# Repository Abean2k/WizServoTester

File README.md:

# WizServoTester

A servo controller PCB that can control up to 4 servos using onboard rotary encoders. Powered by an ESP32-C6 with two power input modes, USB and FTC 12V Battery. 

## Design and Inspo:
I wanted to solve the issue that my team and many other FTC teams I know have. When testing Gobiulda Servos (such as during Robot In 3 Days) we need a fast way to move multiple servos without using code. 
Currently, the only solution available is from Gobiulda, and the full kit for 4 servos cost about $200. So, I made WizServotester!

When designing this I made sure to keep it useful to FTC teams by allowing teams to use their existing battery to power the device. Teams already have many 12v 10 cell batteries, so I have included the xt30 connector that all these batteries have and a buck converter to step the voltage down to 5v for use in the circuit. The entire thing can be reprogrammed using the USBc and inbuilt USB programmer on the ESP32-C6. 

### Power:
This thing can be powered in two ways - USB & Battery. When under battery power all 4 servos can be used at full load and in both continuous and normal modes. However, when in USB power, only 1 servo can be used at one time. This is due to the limited power capacity of a USB C cable. Power can be selected using a switch on the pcb.  

## PCB:
I made a 2 layered PCB on Kicad for the servo tester. The pcb is around 100mm by 60mm. I have included some instructions on how to use the power switch and battery connector as well as some PCB Art (my first time trying that out <3). 

### Schematic

### PCB Layout

## Case:
This is optional, if you are recreating this project, you can choose to use my case or just not use a case. Made with two parts, a base, and a top cover type thing. Uses m3 screws to fasten the PCB into the case and the bottom of the base to the top. Designed on Onshape. 

## Firmware:
The ESP32 will run C++ with Arduino. The code is still under development. The idea is that the code can detect the voltage of the USDB to see where it's receiving power from, then it can control the servos based on the position of the rotary encoder. Lots of the code is similar to my rocketry airbrake project so V1 code development was quick. The online app that is hosted on the ESP will be added based on how the PCB performs and feedback I receive from my team about the tester. 

## Bill of Materials (BOM)

| Part | Quantity | Retailer | Total Price |
|---|---|---|---|
| ESP32-C6-WROOM-1 | 1x5 | LCSC | $21.16 |
| SMD Caps (10u, 100n, 1u, 22u) | 9 x 5 | Already have | $0.00 |
| 470u 16v Capacitor | 1x5 | LCSC | $0.61 |
| ESD9B3.3 Diode | 2x5 | LCSC | $0.53 |
| SS34 Schottky Diode | 1x5 | LCSC | $0.71 |
| SS54 Schottky Diode | 1x5 | LCSC | $0.45 |
| USB-C Receptacle | 1x5 | LCSC | $0.62 |
| XT30 Battery Connector | 1x5 | AliExpress | $2.97 |
| (01x03) Male 90 Degree Header | 4x5 | AliExpress | $5.58 |
| Resistors (10k, 5.1k, 4.7k) | 30 | Already have | $0.00 |
| EC11 Rotary Encoder | 4x5 | AliExpress | $3.24 |
| Push Button Switch | 2x5 | LCSC | $0.53 |
| SPDT Power Select Switch ($1.84) | 1x5 | LCSC | $1.84 |
| USBLC6-2SC6 (USB Protection) | 1x5 | LCSC | $0.48 |
| AMS1117-3.3 (LDO) | 1x5 | LCSC | $0.49 |
| Mini560 Buck Converter | 1x5 | AliExpress | $4.40 |
| PCB (5x boards) | 1x5 | LCSC | $11.32 |

**Taxes & Shipping: AliExpress ($0.96) + LCSC ($10.80)** 

**Total Cost For 5 PCBS: $66.69**

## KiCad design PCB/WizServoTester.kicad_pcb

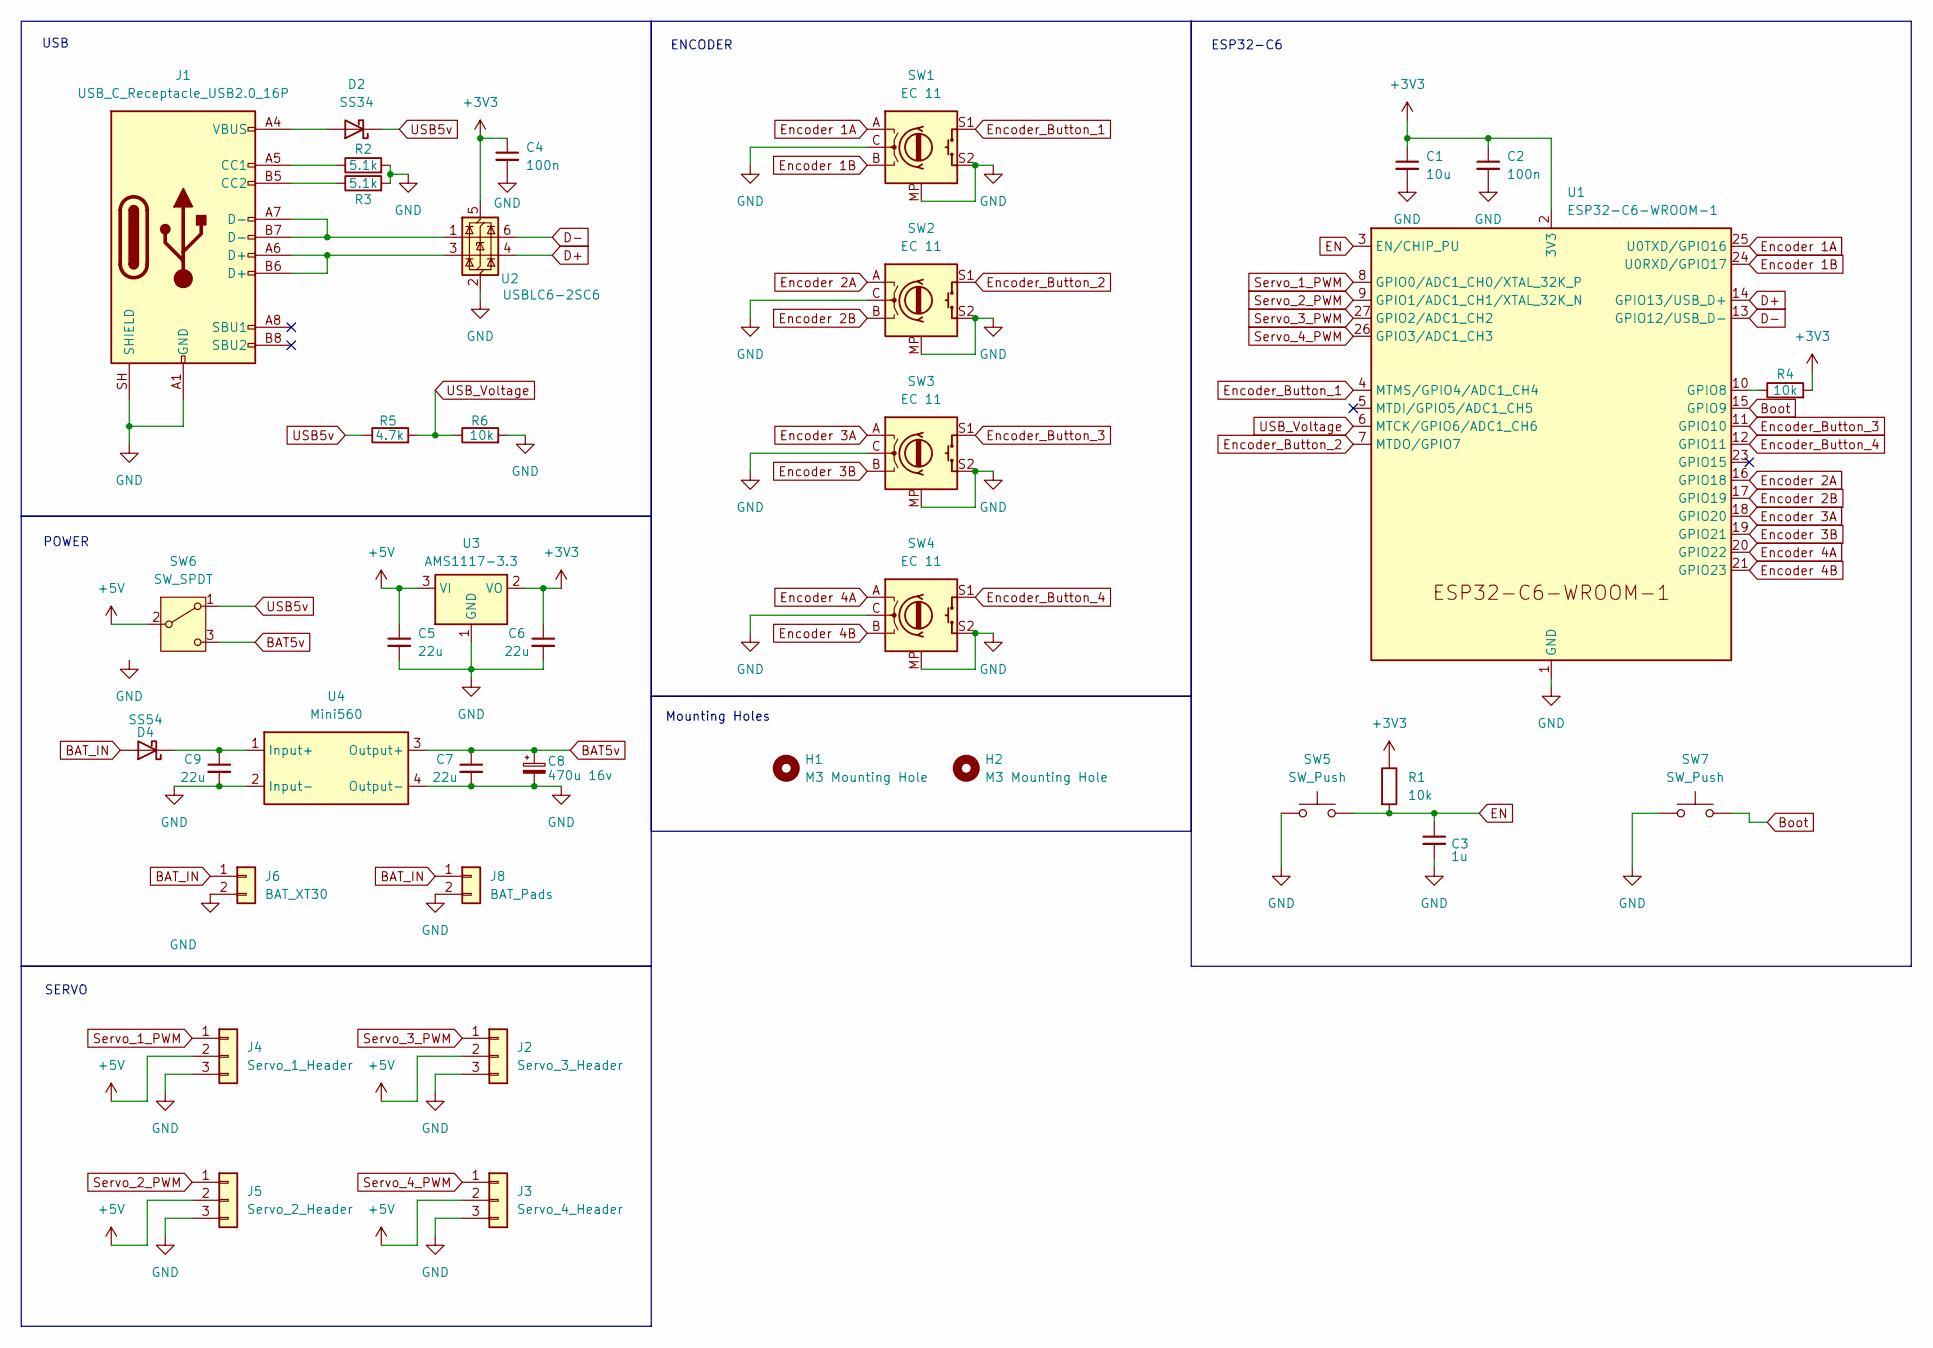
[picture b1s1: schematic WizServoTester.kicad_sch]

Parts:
C1: 10u; C_0805_2012Metric
C2, C4: 100n; C_0805_2012Metric
C3: 1u; C_0805_2012Metric
C5, C6, C7, C9: 22u; C_0805_2012Metric
C8: 470u 16v; CP_Elec_8x10.5
D2: SS34; D_SMA
D4: SS54; D_SMA
H1, H2: M3 Mounting Hole; MountingHole_3.2mm_M3
J1: USB_C_Receptacle_USB2.0_16P; USB_C_Receptacle_HCTL_HC-TYPE-C-16P-01A
J2: Servo_3_Header; PinHeader_1x03_P2.54mm_Horizontal
J3: Servo_4_Header; PinHeader_1x03_P2.54mm_Horizontal
J4: Servo_1_Header; PinHeader_1x03_P2.54mm_Horizontal
J5: Servo_2_Header; PinHeader_1x03_P2.54mm_Horizontal
J6: BAT_XT30; AMASS_XT30U-F_1x02_P5.0mm_Vertical
J8: BAT_Pads; TestPoint_2Pads_Pitch5.08mm_Drill1.3mm
R1, R4, R6: 10k; R_0805_2012Metric
R2, R3: 5.1k; R_0805_2012Metric
R5: 4.7k; R_0805_2012Metric
SW1, SW2, SW3, SW4: EC 11; RotaryEncoder_Alps_EC11E-Switch_Vertical_H20mm_MountingHoles
SW5, SW7: SW_Push; SW_SPST_TS-1088-xR020
SW6: SW_SPDT; SW-TH_XKB_SS-12M11XX
U1: ESP32-C6-WROOM-1
U2: USBLC6-2SC6; SOT-23-6
U3: AMS1117-3.3; SOT-223-3_TabPin2
U4: Mini560; mini650

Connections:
+3V3: C1.1, C2.1, C4.1, C6.1, R1.1, R4.2, U1.2 (3V3), U2.5 (VBUS), U3.2 (VO)
+5V: C5.1, J2.2, J3.2, J4.2, J5.2, SW6.2 (B), U3.3 (VI)
BAT5v: C7.1, C8.1, SW6.3 (C), U4.3 (Output+)
BAT_IN: D4.2 (A), J6.1, J8.1
Boot: SW7.2, U1.15 (GPIO9)
D+: U1.14 (GPIO13/USB_D+), U2.4 (I/O2)
D-: U1.13 (GPIO12/USB_D-), U2.6 (I/O1)
EN: C3.1, R1.2, SW5.2, U1.3 (EN/CHIP_PU)
Encoder 1A: SW1.A, U1.25 (U0TXD/GPIO16)
Encoder 1B: SW1.B, U1.24 (U0RXD/GPIO17)
Encoder 2A: SW2.A, U1.16 (GPIO18)
Encoder 2B: SW2.B, U1.17 (GPIO19)
Encoder 3A: SW3.A, U1.18 (GPIO20)
Encoder 3B: SW3.B, U1.19 (GPIO21)
Encoder 4A: SW4.A, U1.20 (GPIO22)
Encoder 4B: SW4.B, U1.21 (GPIO23)
Encoder_Button_1: SW1.S1, U1.4 (MTMS/GPIO4/ADC1_CH4)
Encoder_Button_2: SW2.S1, U1.7 (MTDO/GPIO7)
Encoder_Button_3: SW3.S1, U1.11 (GPIO10)
Encoder_Button_4: SW4.S1, U1.12 (GPIO11)
GND: C1.2, C2.2, C3.2, C4.2, C5.2, C6.2, C7.2, C8.2, C9.2, J1.A1 (GND), J1.A12 (GND), J1.B1 (GND), J1.B12 (GND), J1.SH (SHIELD), J2.3, J3.3, J4.3, J5.3, J6.2, J8.2, R2.2, R3.2, R6.2, SW1.C, SW1.MP, SW1.S2, SW2.C, SW2.MP, SW2.S2, SW3.C, SW3.MP, SW3.S2, SW4.C, SW4.MP, SW4.S2, SW5.1, SW7.1, U1.1 (GND), U1.28 (GND), U1.29 (GND), U2.2 (GND), U3.1 (GND), U4.2 (Input-), U4.4 (Output-)
unnamed: D2.2 (A), J1.A4 (VBUS), J1.A9 (VBUS), J1.B4 (VBUS), J1.B9 (VBUS)
unnamed: C9.1, D4.1 (K), U4.1 (Input+)
unnamed: J1.A5 (CC1), R2.1
unnamed: J1.B5 (CC2), R3.1
unnamed: J1.A6 (D+), J1.B6 (D+), U2.3 (I/O2)
unnamed: J1.A7 (D-), J1.B7 (D-), U2.1 (I/O1)
unnamed: R4.1, U1.10 (GPIO8)
Servo_1_PWM: J4.1, U1.8 (GPIO0/ADC1_CH0/XTAL_32K_P)
Servo_2_PWM: J5.1, U1.9 (GPIO1/ADC1_CH1/XTAL_32K_N)
Servo_3_PWM: J2.1, U1.27 (GPIO2/ADC1_CH2)
Servo_4_PWM: J3.1, U1.26 (GPIO3/ADC1_CH3)
USB5v: D2.1 (K), R5.1, SW6.1 (A)
USB_Voltage: R5.2, R6.1, U1.6 (MTCK/GPIO6/ADC1_CH6)

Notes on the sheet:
ESP32-C6
ENCODER
POWER
USB
SERVO
Mounting Holes

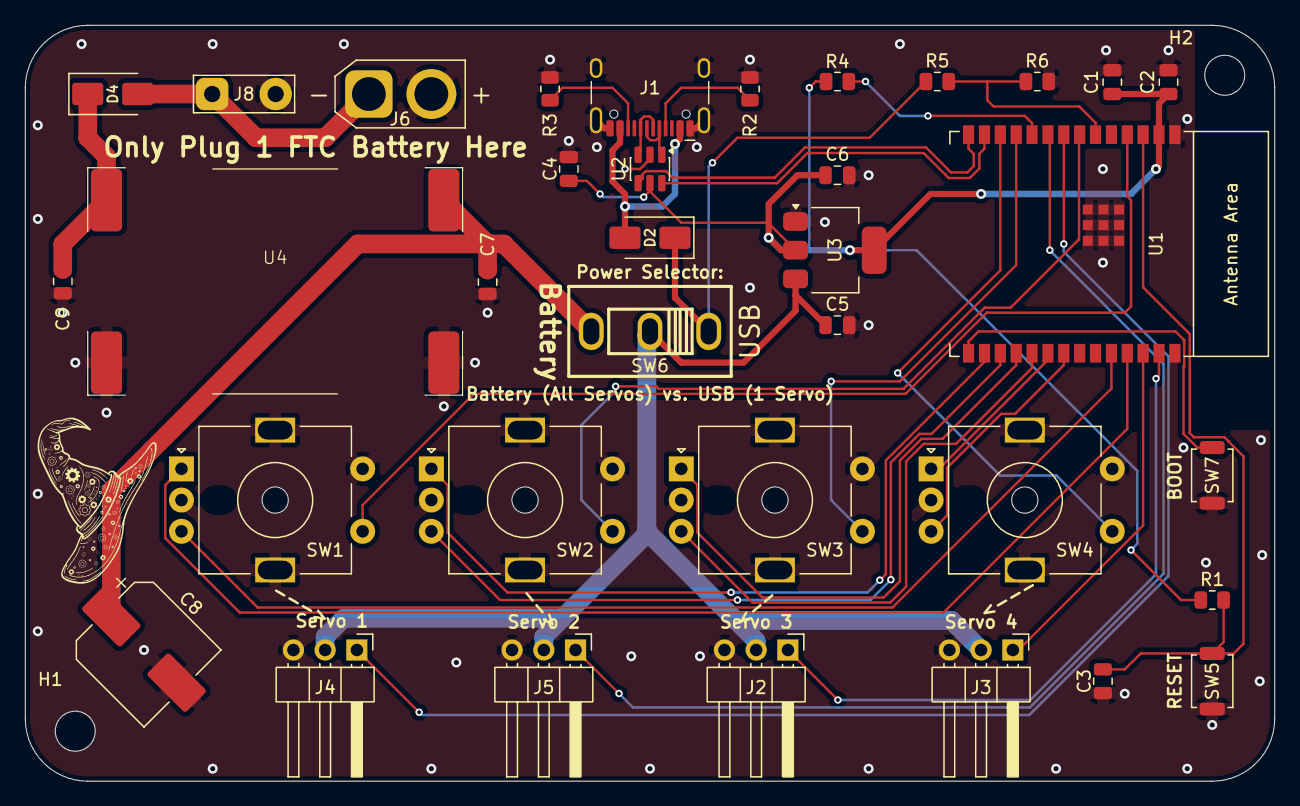
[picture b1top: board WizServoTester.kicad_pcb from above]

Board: 2 copper layers, 100.0 x 60.5 mm, 37 parts (0 on the bottom side), 34 nets.

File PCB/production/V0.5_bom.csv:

Designator,Footprint,Quantity,Value,LCSC Part #
C1,0805,1,10u,
"C2, C4",0805,2,100n,
C3,0805,1,1u,
"C5, C6, C7, C9",0805,4,22u,
C8,CP_Elec_10x10.5,1,1000u 16v,
"D1, D3",D_SOD-923,2,ESD9B3.3,
D2,D_SMA,1,SS34,
D4,D_SMA,1,SS54,
J1,USB_C_Receptacle_HCTL_HC-TYPE-C-16P-01A,1,USB_C_Receptacle_USB2.0_16P,
J2,PinHeader_1x03_P2.54mm_Horizontal,1,Servo_3_Header,
J3,PinHeader_1x03_P2.54mm_Horizontal,1,Servo_4_Header,
J4,PinHeader_1x03_P2.54mm_Horizontal,1,Servo_1_Header,
J5,PinHeader_1x03_P2.54mm_Horizontal,1,Servo_2_Header,
J6,AMASS_XT30U-F_1x02_P5.0mm_Vertical,1,BAT_XT30,
J8,TestPoint_2Pads_Pitch5.08mm_Drill1.3mm,1,BAT_Pads,
"R1, R4, R6",0805,3,10k,
"R2, R3",0805,2,5.1k,
R5,0805,1,4.7k,
"SW1, SW2, SW3, SW4",RotaryEncoder_Alps_EC11E-Switch_Vertical_H20mm_MountingHoles,4,EC 11,
"SW5, SW7",SW_SPST_TS-1088-xR020,2,SW_Push,
SW6,SW-TH_XKB_SS-12M11XX,1,SW_SPDT,C2879832
U1,ESP32-C6-WROOM-1,1,ESP32-C6-WROOM-1,
U2,SOT-23-6,1,USBLC6-2SC6,
U3,SOT-223-3_TabPin2,1,AMS1117-3.3,
U4,mini650,1,Mini560,
